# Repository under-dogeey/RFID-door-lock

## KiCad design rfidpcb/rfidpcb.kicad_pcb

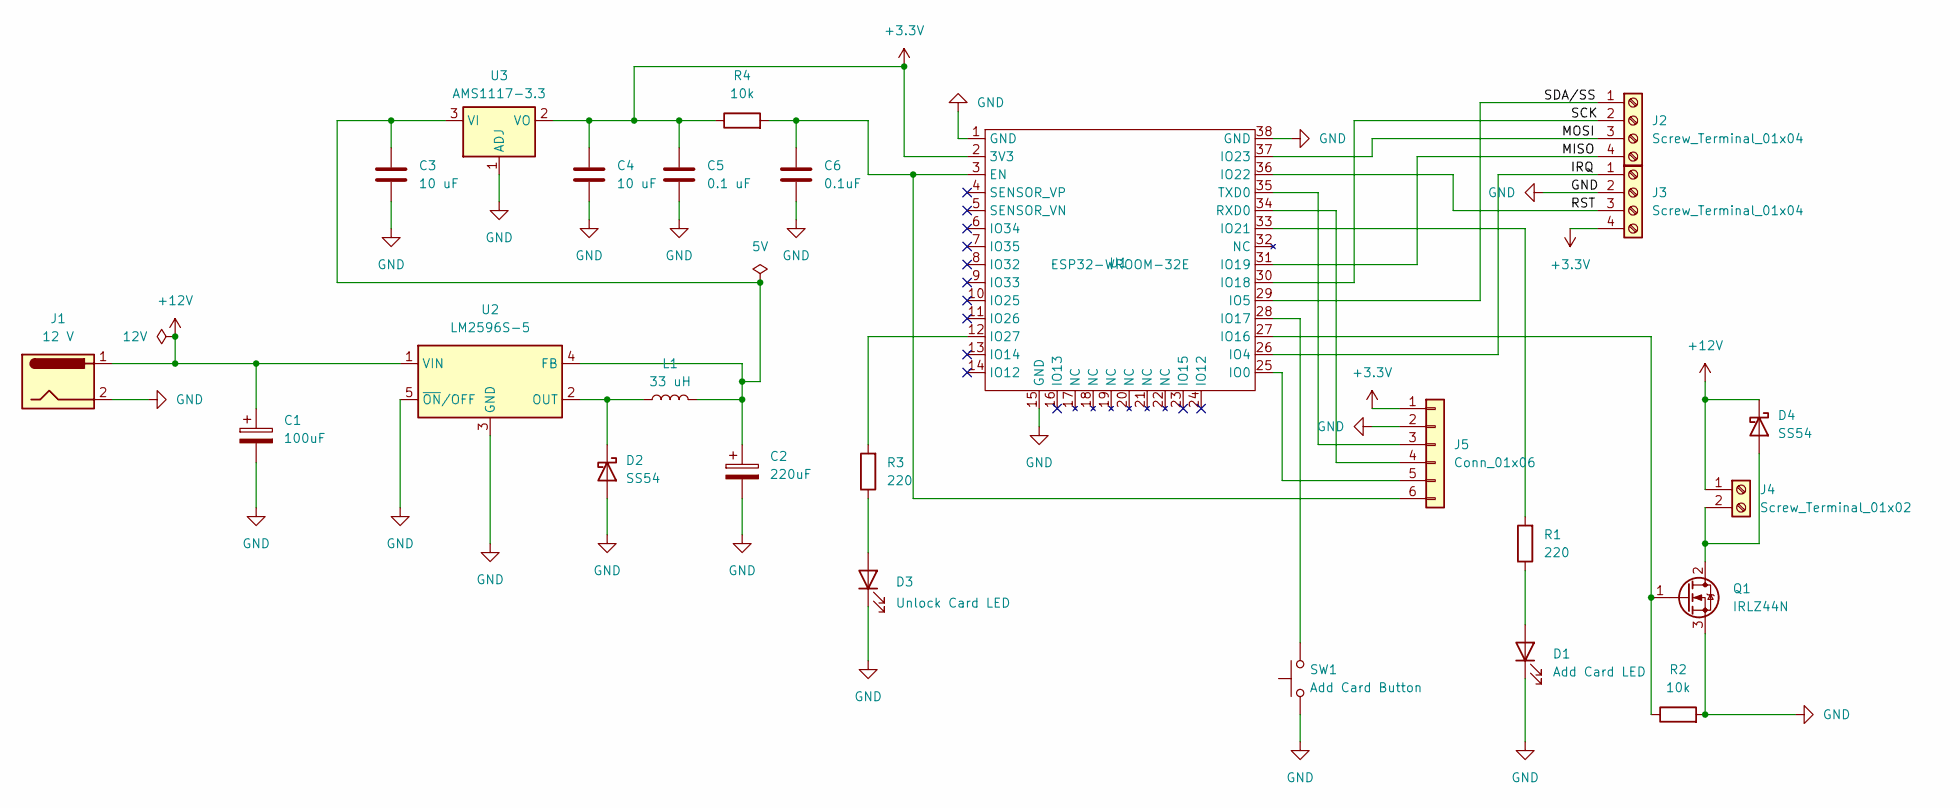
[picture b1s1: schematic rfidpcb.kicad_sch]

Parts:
C1: 100uF; CP_Elec_8x10.5
C2: 220uF; CP_Elec_8x10.5
C3, C4: 10 uF; C_0805_2012Metric
C5: 0.1 uF; C_0805_2012Metric
C6: 0.1uF; C_0805_2012Metric
D1: Add Card LED; LED_0805_2012Metric
D2, D4: SS54; D_SMA
D3: Unlock Card LED; LED_0805_2012Metric
J1: 12 V; BarrelJack_Horizontal
J2, J3: Screw_Terminal_01x04; TerminalBlock_Phoenix_MKDS-3-4-5.08_1x04_P5.08mm_Horizontal
J4: Screw_Terminal_01x02; TerminalBlock_Phoenix_MKDS-3-2-5.08_1x02_P5.08mm_Horizontal
J5: Conn_01x06; PinHeader_1x06_P2.54mm_Vertical
L1: 33 uH; L_6.3x6.3_H3
Q1: IRLZ44N; TO-220-3_Vertical
R1, R3: 220; R_0805_2012Metric
R2, R4: 10k; R_0805_2012Metric
SW1: Add Card Button; SW_Push_1TS009xxxx-xxxx-xxxx_6x6x5mm
U1: ESP32-WROOM-32E
U2: LM2596S-5; TO-263-5_TabPin3
U3: AMS1117-3.3; SOT-223-3_TabPin2

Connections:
+3.3V: C4.1, C5.2, J3.4, J5.1, R4.1, U1.2 (3V3), U3.2 (VO)
+12V: C1.1, D4.1 (K), J1.1, J4.1, U2.1 (VIN)
/IRQ: J3.1, U1.26 (IO4)
/MISO: J2.4, U1.31 (IO19)
/MOSI: J2.3, U1.37 (IO23)
/RST: J3.3, U1.36 (IO22)
/SCK: J2.2, U1.30 (IO18)
/SDA/SS: J2.1, U1.29 (IO5)
GND: C1.2, C2.2, C3.1, C4.2, C5.1, C6.2, D1.1 (K), D2.2 (A), D3.1 (K), J1.2, J3.2, J5.2, Q1.3 (S), R2.2, SW1.1, U1.1 (GND), U1.15 (GND), U1.38 (GND), U2.3 (GND), U2.5 (~ON/OFF), U3.1 (ADJ)
unnamed: D1.2 (A), R1.1
unnamed: D2.1 (K), L1.1, U2.2 (OUT)
unnamed: D3.2 (A), R3.1
unnamed: D4.2 (A), J4.2, Q1.2 (D)
unnamed: J5.3, U1.35 (TXD0)
unnamed: J5.4, U1.34 (RXD0)
unnamed: J5.5, U1.25 (IO0)
unnamed: C6.1, J5.6, R4.2, U1.3 (EN)
unnamed: Q1.1 (G), R2.1, U1.27 (IO16)
unnamed: SW1.2, U1.28 (IO17)
unnamed: R1.2, U1.33 (IO21)
unnamed: R3.2, U1.12 (IO27)
unnamed: C2.1, C3.2, L1.2, U2.4 (FB), U3.3 (VI)

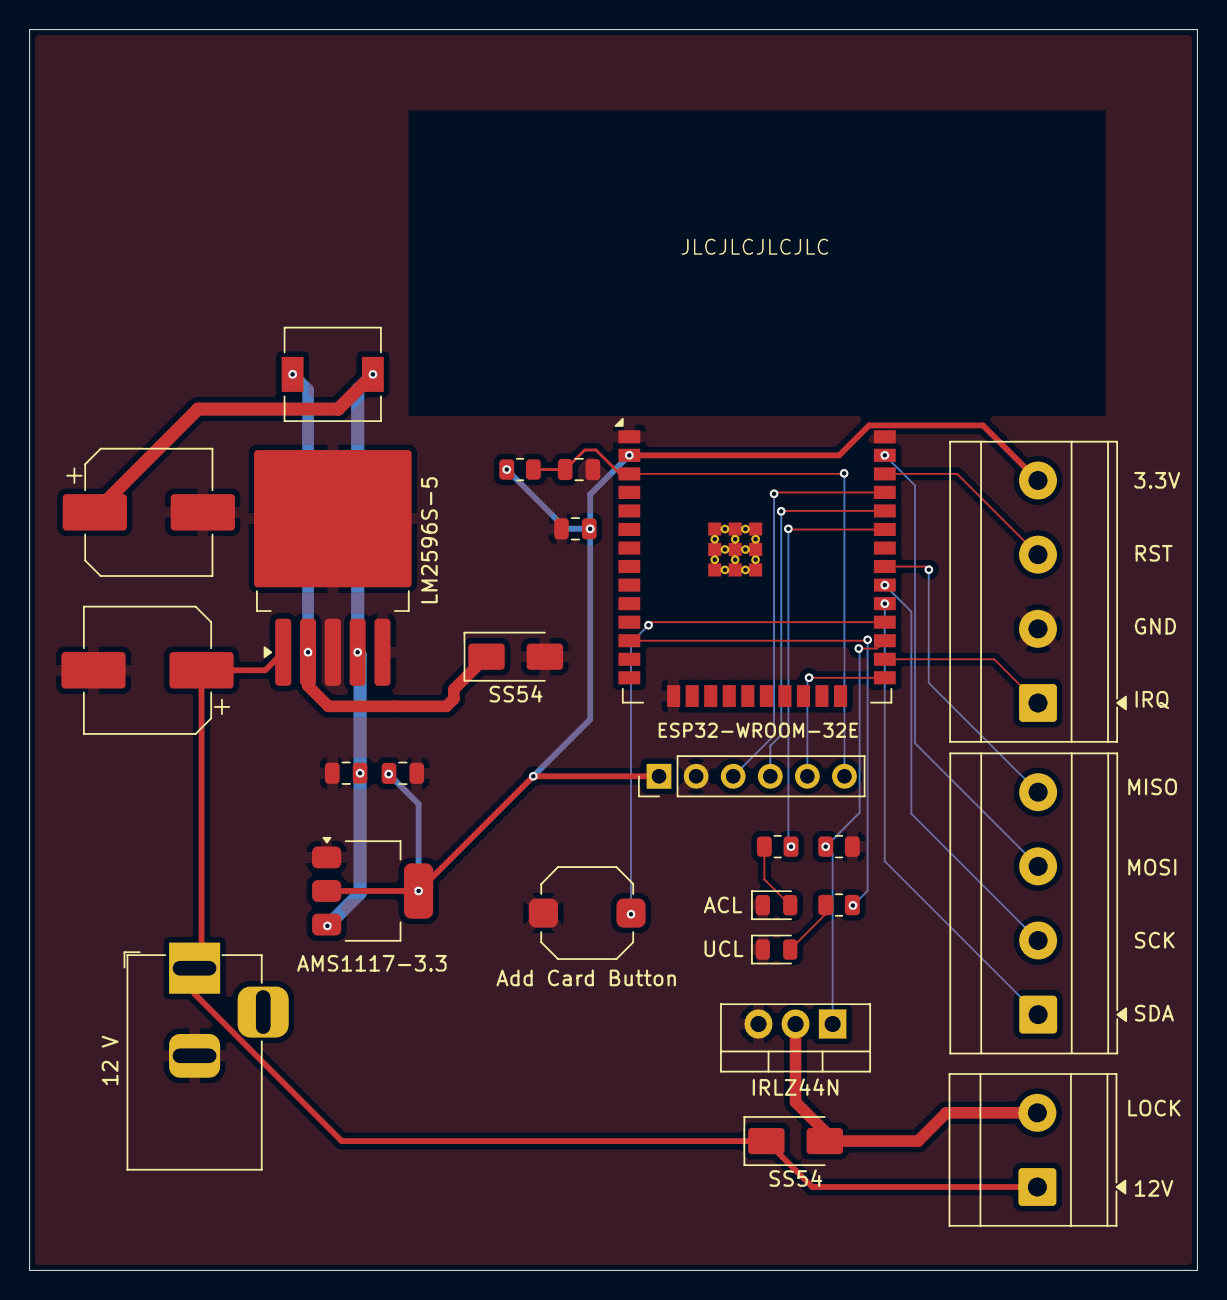
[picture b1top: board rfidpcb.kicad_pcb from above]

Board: 4 copper layers, 80.0 x 85.0 mm, 25 parts (0 on the bottom side), 22 nets.

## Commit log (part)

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2026-06-20 initial commit with python database set up
2026-06-20 added ino file containing esp32 functionality
2026-06-21 added the database to store ids to fastapi server
2026-06-21 updated function to get all ids in the table
2026-06-21 replaced polling with interrupt when checking cards on the reader
2026-06-30 added timeout when adding a card
